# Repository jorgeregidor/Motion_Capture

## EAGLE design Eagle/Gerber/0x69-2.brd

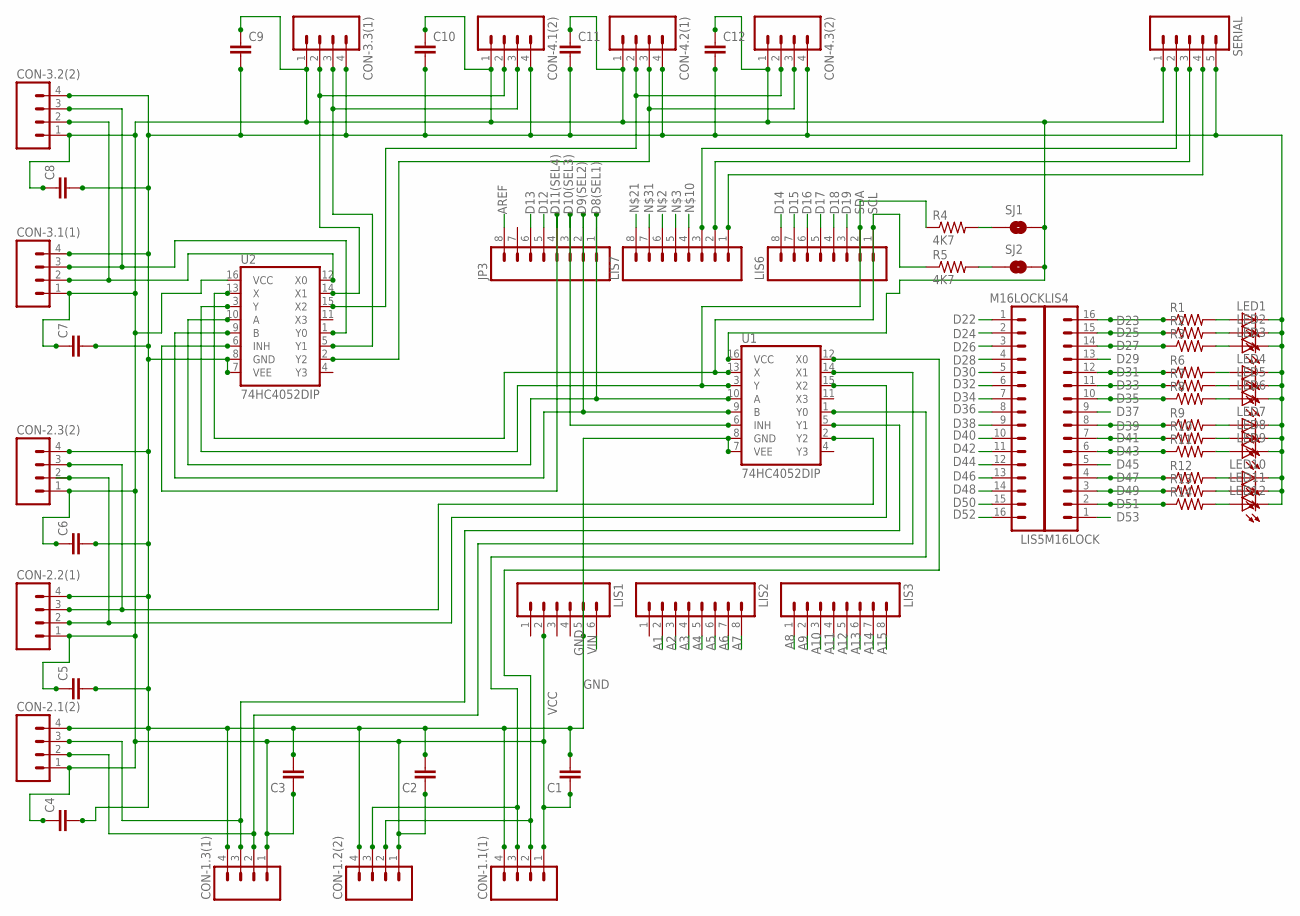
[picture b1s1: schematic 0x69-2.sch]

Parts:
C1, C2, C3, C4, C5, C6, C7, C8, C9, C10, C11, C12: C; C0805
CON-1.1(1), CON-1.2(2), CON-1.3(1), CON-2.1(2), CON-2.2(1), CON-2.3(2), CON-3.1(1), CON-3.2(2), CON-3.3(1), CON-4.1(2), CON-4.2(1), CON-4.3(2): M04LONGPADS; 1X04_LONGPADS
JP3: M08LOCK; 1X08_LOCK
LED1, LED2, LED3, LED4, LED5, LED6, LED7, LED8, LED9, LED10, LED11, LED12: LED-FKIT-1206; FKIT-LED-1206
LIS1: M06LOCK; 1X06_LOCK
LIS2, LIS3, LIS6, LIS7: M08LOCK; 1X08_LOCK
LIS4, LIS5: M16LOCK; 1X16_LOCK
R1, R2, R3, R6, R7, R8, R9, R10, R11, R12, R13, R14: 0.22OHM1/4W1%(0805); 0805
R4, R5: 4K7; 0603-RES
SERIAL: M05PTH_LONGPADS; 1X05_LONGPADS
SJ1, SJ2: SOLDERJUMPERNC; SJ-NC
U1, U2: 74HC4052DIP; DIL16

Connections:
A1: LIS2.2
A2: LIS2.3
A3: LIS2.4
A4: LIS2.5
A5: LIS2.6
A6: LIS2.7
A7: LIS2.8
A8: LIS3.1
A9: LIS3.2
A10: LIS3.3
A11: LIS3.4
A12: LIS3.5
A13: LIS3.6
A14: LIS3.7
A15: LIS3.8
AREF: JP3.8
D8(SEL1): JP3.1, U1.10 (A), U2.10 (A)
D9(SEL2): JP3.2, U1.9 (B), U2.9 (B)
D10(SEL3): JP3.3, U1.6 (INH)
D11(SEL4): JP3.4, U2.6 (INH)
D12: JP3.5
D13: JP3.6
D14: LIS6.8
D15: LIS6.7
D16: LIS6.6
D17: LIS6.5
D18: LIS6.4
D19: LIS6.3
D22: LIS5.1
D23: LIS4.16, R1.1
D24: LIS5.2
D25: LIS4.15, R2.1
D26: LIS5.3
D27: LIS4.14, R3.1
D28: LIS5.4
D29: LIS4.13
D30: LIS5.5
D31: LIS4.12, R6.1
D32: LIS5.6
D33: LIS4.11, R7.1
D34: LIS5.7
D35: LIS4.10, R8.1
D36: LIS5.8
D37: LIS4.9
D38: LIS5.9
D39: LIS4.8, R9.1
D40: LIS5.10
D41: LIS4.7, R10.1
D42: LIS5.11
D43: LIS4.6, R11.1
D44: LIS5.12
D45: LIS4.5
D46: LIS5.13
D47: LIS4.4, R12.1
D48: LIS5.14
D49: LIS4.3, R13.1
D50: LIS5.15
D51: LIS4.2, R14.1
D52: LIS5.16
D53: LIS4.1
GND: C1.2, C2.2, C3.2, C4.2, C5.2, C6.2, C7.2, C8.2, C9.2, C10.2, C11.2, C12.2, CON-1.1(1).4, CON-1.2(2).4, CON-1.3(1).4, CON-2.1(2).4, CON-2.2(1).4, CON-2.3(2).4, CON-3.1(1).4, CON-3.2(2).4, CON-3.3(1).4, CON-4.1(2).4, CON-4.2(1).4, CON-4.3(2).4, LED1.C, LED2.C, LED3.C, LED4.C, LED5.C, LED6.C, LED7.C, LED8.C, LED9.C, LED10.C, LED11.C, LED12.C, LIS1.5, SERIAL.5, U1.7 (VEE), U1.8 (GND), U2.7 (VEE), U2.8 (GND)
MODE: LIS7.3, SERIAL.2
unnamed: R4.2, SJ1.1
unnamed: R5.2, SJ2.1
unnamed: CON-1.1(1).2, CON-1.2(2).2, U1.12 (X0)
unnamed: CON-1.1(1).3, CON-1.2(2).3, U1.1 (Y0)
unnamed: CON-4.2(1).2, CON-4.3(2).2, U2.15 (X2)
unnamed: CON-1.3(1).2, CON-2.1(2).2, U1.14 (X1)
unnamed: CON-1.3(1).3, CON-2.1(2).3, U1.5 (Y1)
unnamed: CON-2.2(1).2, CON-2.3(2).2, U1.15 (X2)
unnamed: LED1.A, R1.2
unnamed: LED2.A, R2.2
unnamed: LED3.A, R3.2
unnamed: CON-2.2(1).3, CON-2.3(2).3, U1.2 (Y2)
unnamed: CON-4.2(1).3, CON-4.3(2).3, U2.2 (Y2)
unnamed: CON-3.1(1).3, CON-3.2(2).3, U2.1 (Y0)
unnamed: CON-3.1(1).2, CON-3.2(2).2, U2.12 (X0)
unnamed: CON-3.3(1).2, CON-4.1(2).2, U2.14 (X1)
unnamed: CON-3.3(1).3, CON-4.1(2).3, U2.5 (Y1)
unnamed: LED4.A, R6.2
unnamed: LED5.A, R7.2
unnamed: LED6.A, R8.2
unnamed: LED7.A, R9.2
unnamed: LED8.A, R10.2
unnamed: LED9.A, R11.2
unnamed: LED10.A, R12.2
unnamed: LED11.A, R13.2
unnamed: LED12.A, R14.2
RX0: LIS7.1, SERIAL.4
SCL: LIS6.1, R5.1, U1.13 (X), U2.13 (X)
SDA: LIS6.2, R4.1, U1.3 (Y), U2.3 (Y)
TX0: LIS7.2, SERIAL.3
VCC: C1.1, C2.1, C3.1, C4.1, C5.1, C6.1, C7.1, C8.1, C9.1, C10.1, C11.1, C12.1, CON-1.1(1).1, CON-1.2(2).1, CON-1.3(1).1, CON-2.1(2).1, CON-2.2(1).1, CON-2.3(2).1, CON-3.1(1).1, CON-3.2(2).1, CON-3.3(1).1, CON-4.1(2).1, CON-4.2(1).1, CON-4.3(2).1, LIS1.2, SERIAL.1, SJ1.2, SJ2.2, U1.16 (VCC), U2.16 (VCC)
VIN: LIS1.6

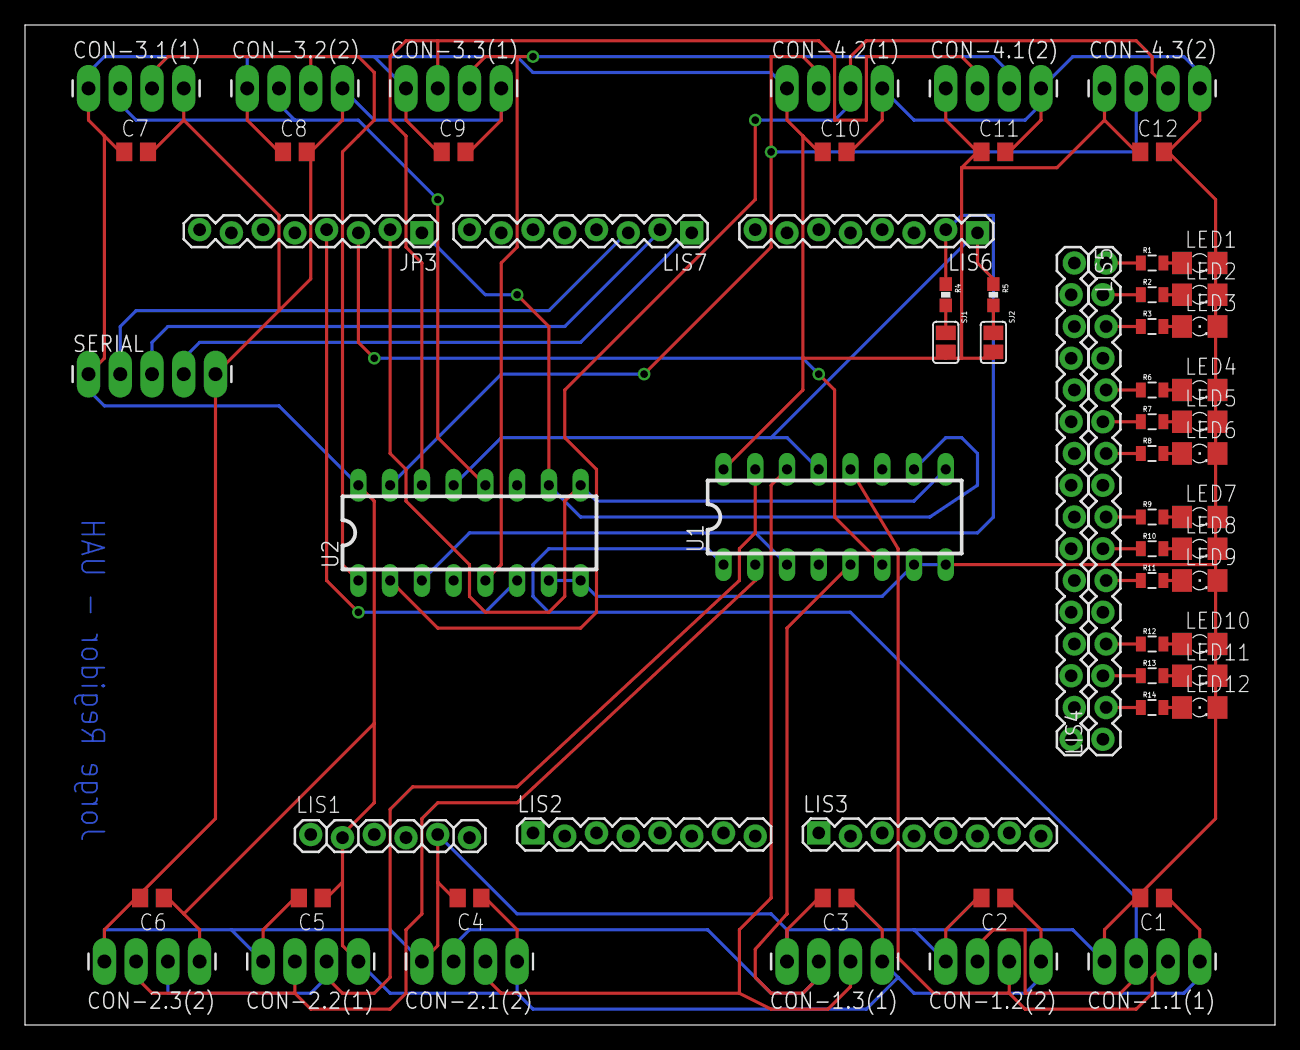
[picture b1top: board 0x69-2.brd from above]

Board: 2 copper layers, 100.0 x 80.0 mm, 63 parts (0 on the bottom side), 49 nets.

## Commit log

2014-03-29 Motion Capture
    The information is in Spanish

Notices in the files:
parts and their libraries:
SparkFun-Connectors: Licensing: CC v3.0 Share-Alike You are welcome to use this library for commercial purposes.
